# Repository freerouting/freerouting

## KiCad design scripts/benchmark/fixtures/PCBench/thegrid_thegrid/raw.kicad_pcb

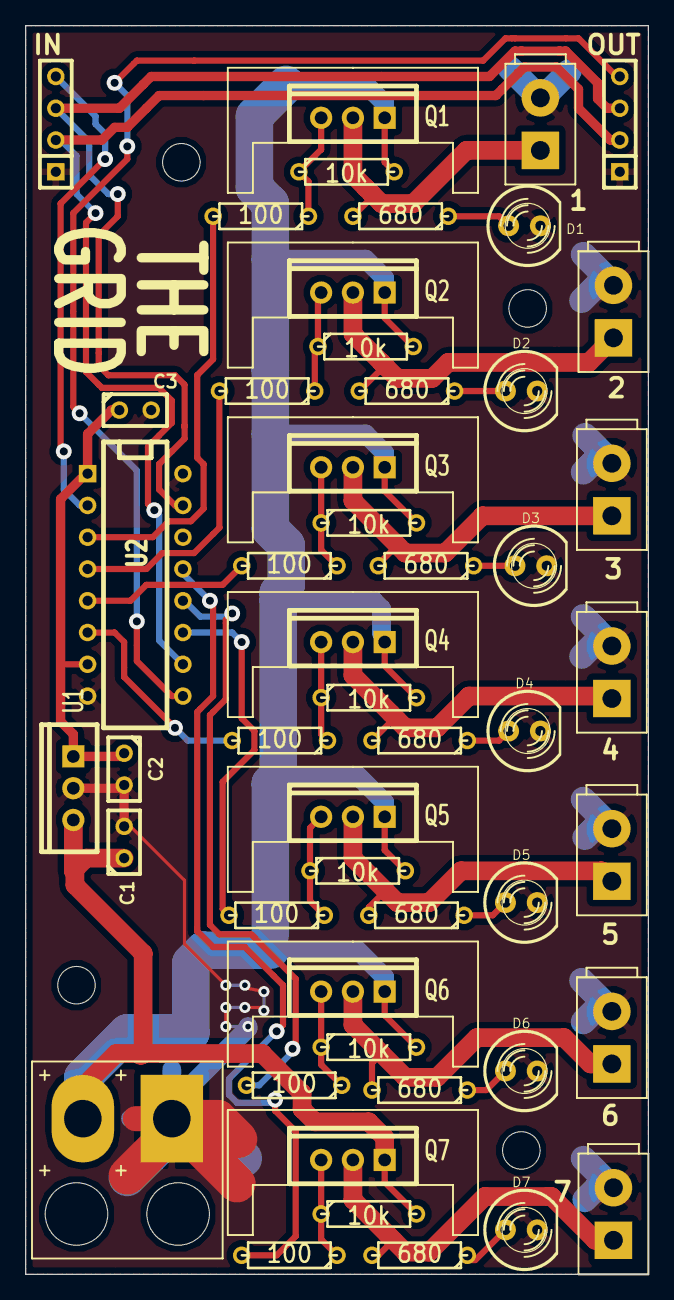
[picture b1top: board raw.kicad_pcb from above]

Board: 2 copper layers, 49.8 x 99.8 mm, 54 parts (0 on the bottom side), 35 nets.

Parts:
C1: .33u; C1
C2: .1u; C1
C3: 100n; C1
D1, D2, D3, D4, D5, D6, D7: LED; LED-5MM
MH: MountingHole_3mm_RevA_Date21Jun2010; MountingHole_3mm
MH#2, MH#3, MH#4: MountingHole_3mm_RevA_Date21Jun2010; MountingHole_3mm
P1: POWER; SIL-2
P2: SHIFT_IN; SIL-4
P3: SHIFT_OUT; SIL-4
P4, P5, P6, P7, P8, P9, P10: CONN_2; SIL-2
Q1, Q2, Q3, Q4, Q5, Q6, Q7: FQP7P06; TO220_VERT
R1, R3, R5, R7, R9, R11, R13: 10k; R3
R2, R4, R6, R8, R10, R12, R14: 100; R3
R15, R16, R17, R18, R19, R20, R21: 680; R3
U1: UA7805CKCS; TO220_VERT
U2: TPIC6C595; DIP-16__300

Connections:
+5V: C2.1, C3.1, U1.1, U2.1, U2.7
+12V: C1.1, P1.2, Q1.1, Q2.1, Q3.1, Q4.1, Q5.1, Q6.1, Q7.1, R1.2, R3.2, R5.2, R7.2, R9.2, R11.2, R13.2, U1.2
GND: C1.2, C2.2, C3.2, D1.2, D2.2, D3.2, D4.2, D5.2, D6.2, D7.2, P1.1, P2.1, P3.1, P4.2, P5.2, P6.2, P7.2, P8.2, P9.2, P10.2, U1.3, U2.8, U2.16
unnamed: D1.1, R15.1
unnamed: D2.1, R16.1
unnamed: D3.1, R17.1
unnamed: D4.1, R18.1
unnamed: D5.1, R19.1
unnamed: D6.1, R20.1
unnamed: D7.1, R21.1
unnamed: P2.2, P3.2, U2.10
unnamed: P2.3, P3.3, U2.15
unnamed: P2.4, U2.2
unnamed: P3.4, U2.9
unnamed: P4.1, Q1.3, R15.2
unnamed: P5.1, Q2.3, R16.2
unnamed: P6.1, Q3.3, R17.2
unnamed: P7.1, Q4.3, R18.2
unnamed: P8.1, Q5.3, R19.2
unnamed: P9.1, Q6.3, R20.2
unnamed: P10.1, Q7.3, R21.2
unnamed: Q1.2, R1.1, R2.1
unnamed: Q2.2, R3.1, R4.1
unnamed: Q3.2, R5.1, R6.1
unnamed: Q4.2, R7.1, R8.1
unnamed: Q5.2, R13.1, R14.1
unnamed: Q6.2, R9.1, R10.1
unnamed: Q7.2, R11.1, R12.1
unnamed: R2.2, U2.3
unnamed: R4.2, U2.4
unnamed: R6.2, U2.5
unnamed: R8.2, U2.6
unnamed: R10.2, U2.12
unnamed: R12.2, U2.13
unnamed: R14.2, U2.11

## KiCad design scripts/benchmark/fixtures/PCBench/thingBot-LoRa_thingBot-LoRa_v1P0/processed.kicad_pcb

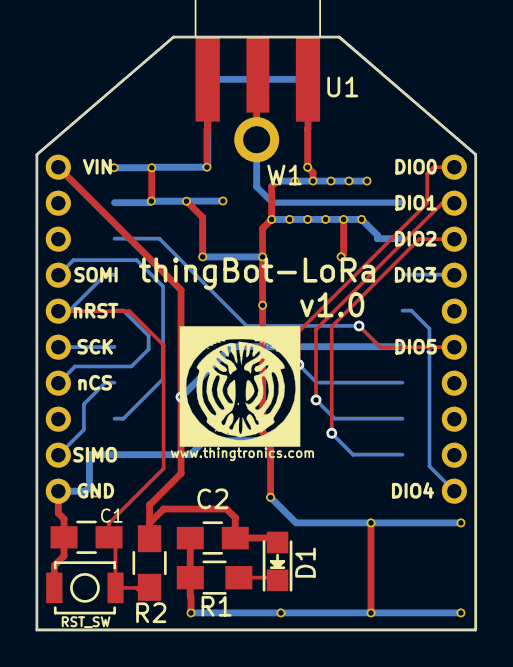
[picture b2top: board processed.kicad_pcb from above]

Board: 2 copper layers, 24.4 x 32.9 mm, 10 parts (1 on the bottom side), 15 nets.

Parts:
C1: 15nF; C_0805_HandSoldering
C2: 0.1uF; C_0805_HandSoldering
D1: POWER; LED_0805
R1, R2: 1K; R_0805_HandSoldering
RST_SW: RESET; SW_SPST_B3U-1000P
U1: EDGE_SMA; EDGE_SMA_5
U2: RFM92/95; RFM92_95_96_98
U3: XBEE_MODULE; Xbee_mod
W1: WIRE_ANT; SolderWirePad_single_2mmDrill

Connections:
ANT: U1.1, U2.9, W1.1
DIO0: U2.14, U3.20
DIO1: U2.15, U3.19
DIO2: U2.16, U3.18
DIO3: U2.11, U3.17
DIO4: U2.12, U3.11
DIO5: U2.7, U3.15
GND: C1.2, C2.2, R1.2, RST_SW.1, U1.2, U1.3, U1.4, U1.5, U2.1, U2.8, U2.10, U3.10
unnamed: D1.1, R1.1
RFM_VIN: C2.1, D1.2, R2.1, U2.13, U3.1
SPI_SCK: U2.4, U3.6
SPI_SIMO: U2.3, U3.9
SPI_SOMI: U2.2, U3.4
SPI_nCS: U2.5, U3.7
nRESET: C1.1, R2.2, RST_SW.2, U2.6, U3.5
